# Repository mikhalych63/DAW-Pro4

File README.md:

This is a project of car audio processor and 8ch amplifier wich use of CamillaDSP project: https://github.com/HEnquist/camilladsp

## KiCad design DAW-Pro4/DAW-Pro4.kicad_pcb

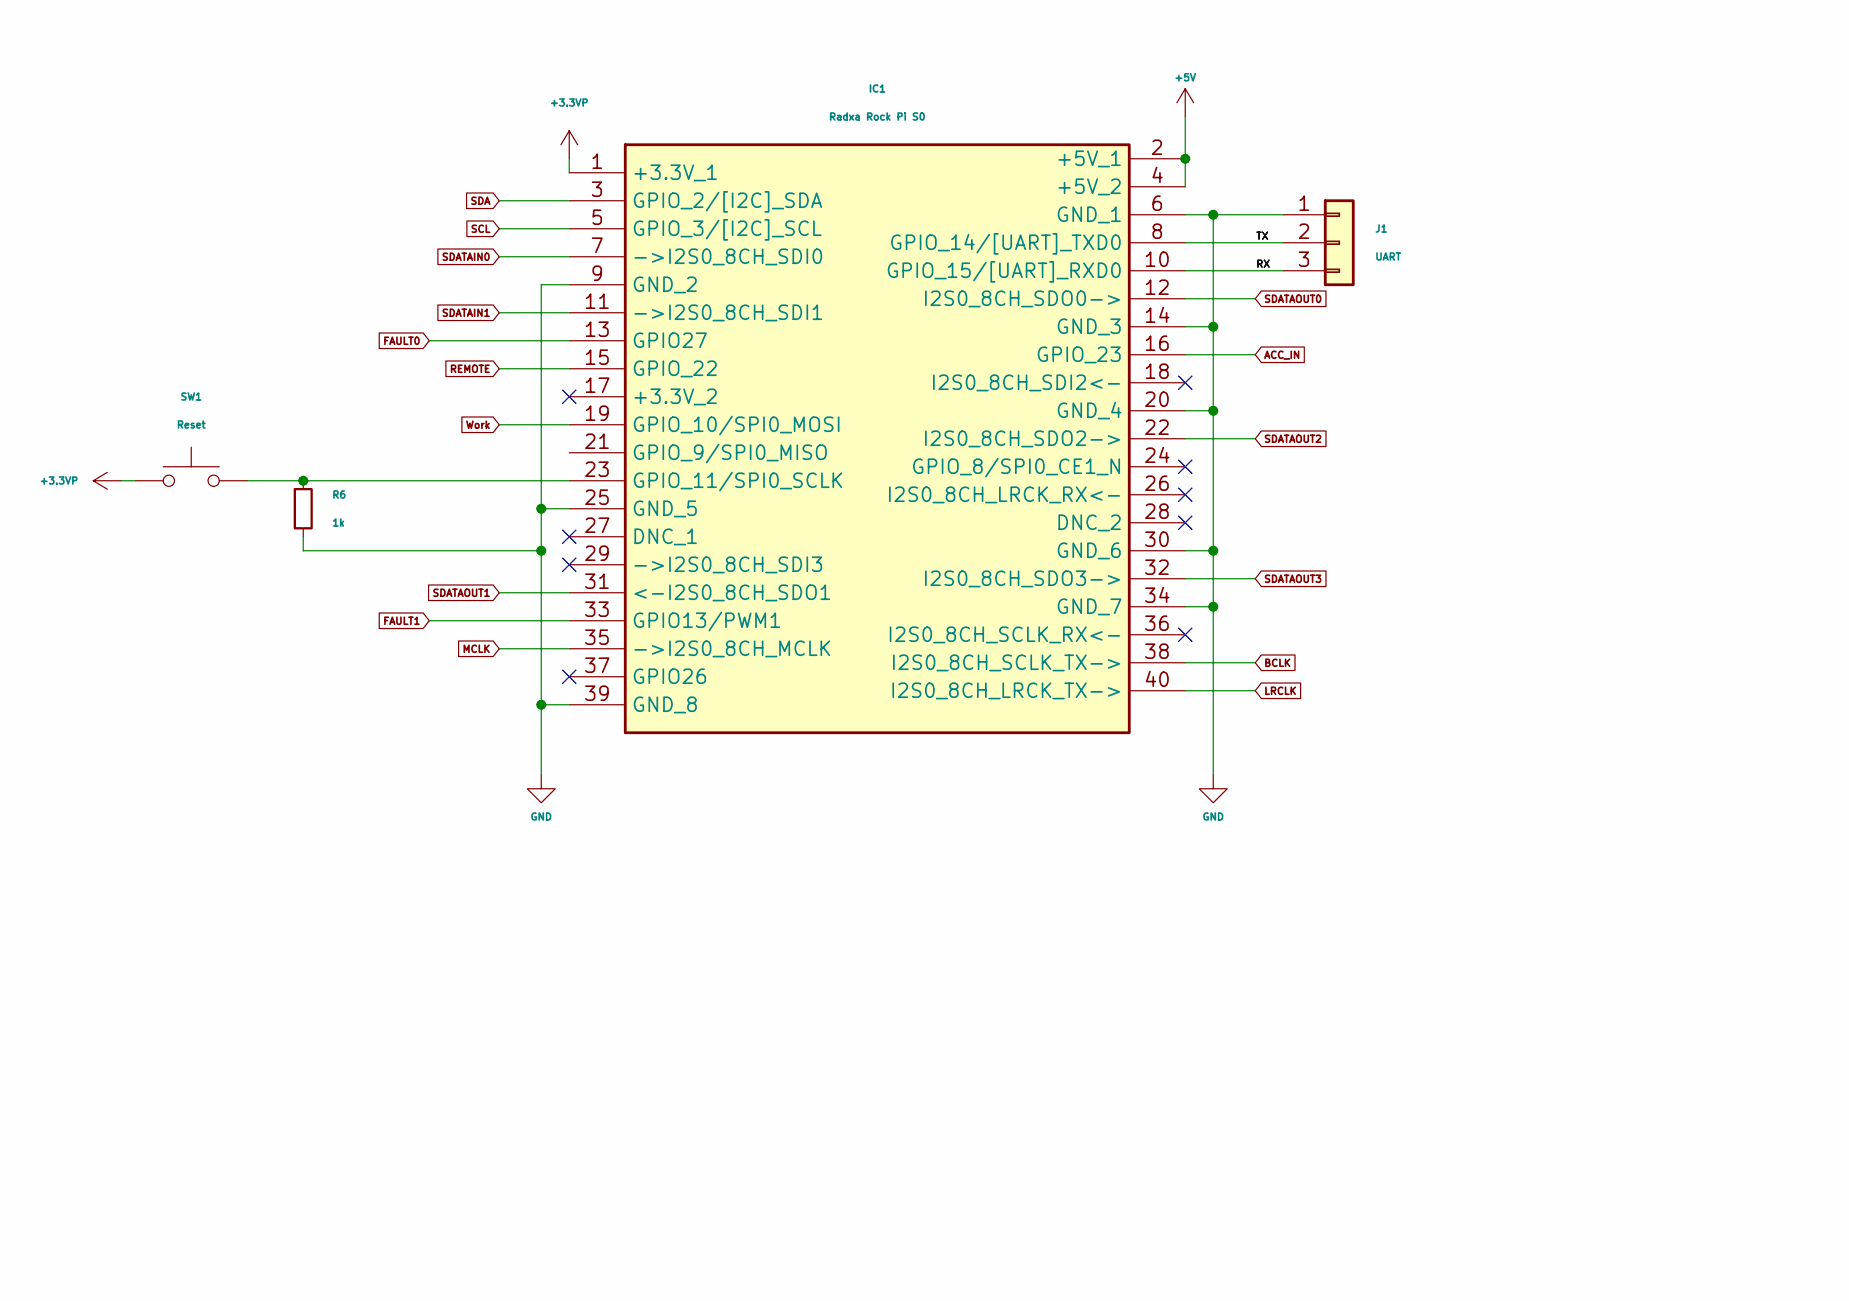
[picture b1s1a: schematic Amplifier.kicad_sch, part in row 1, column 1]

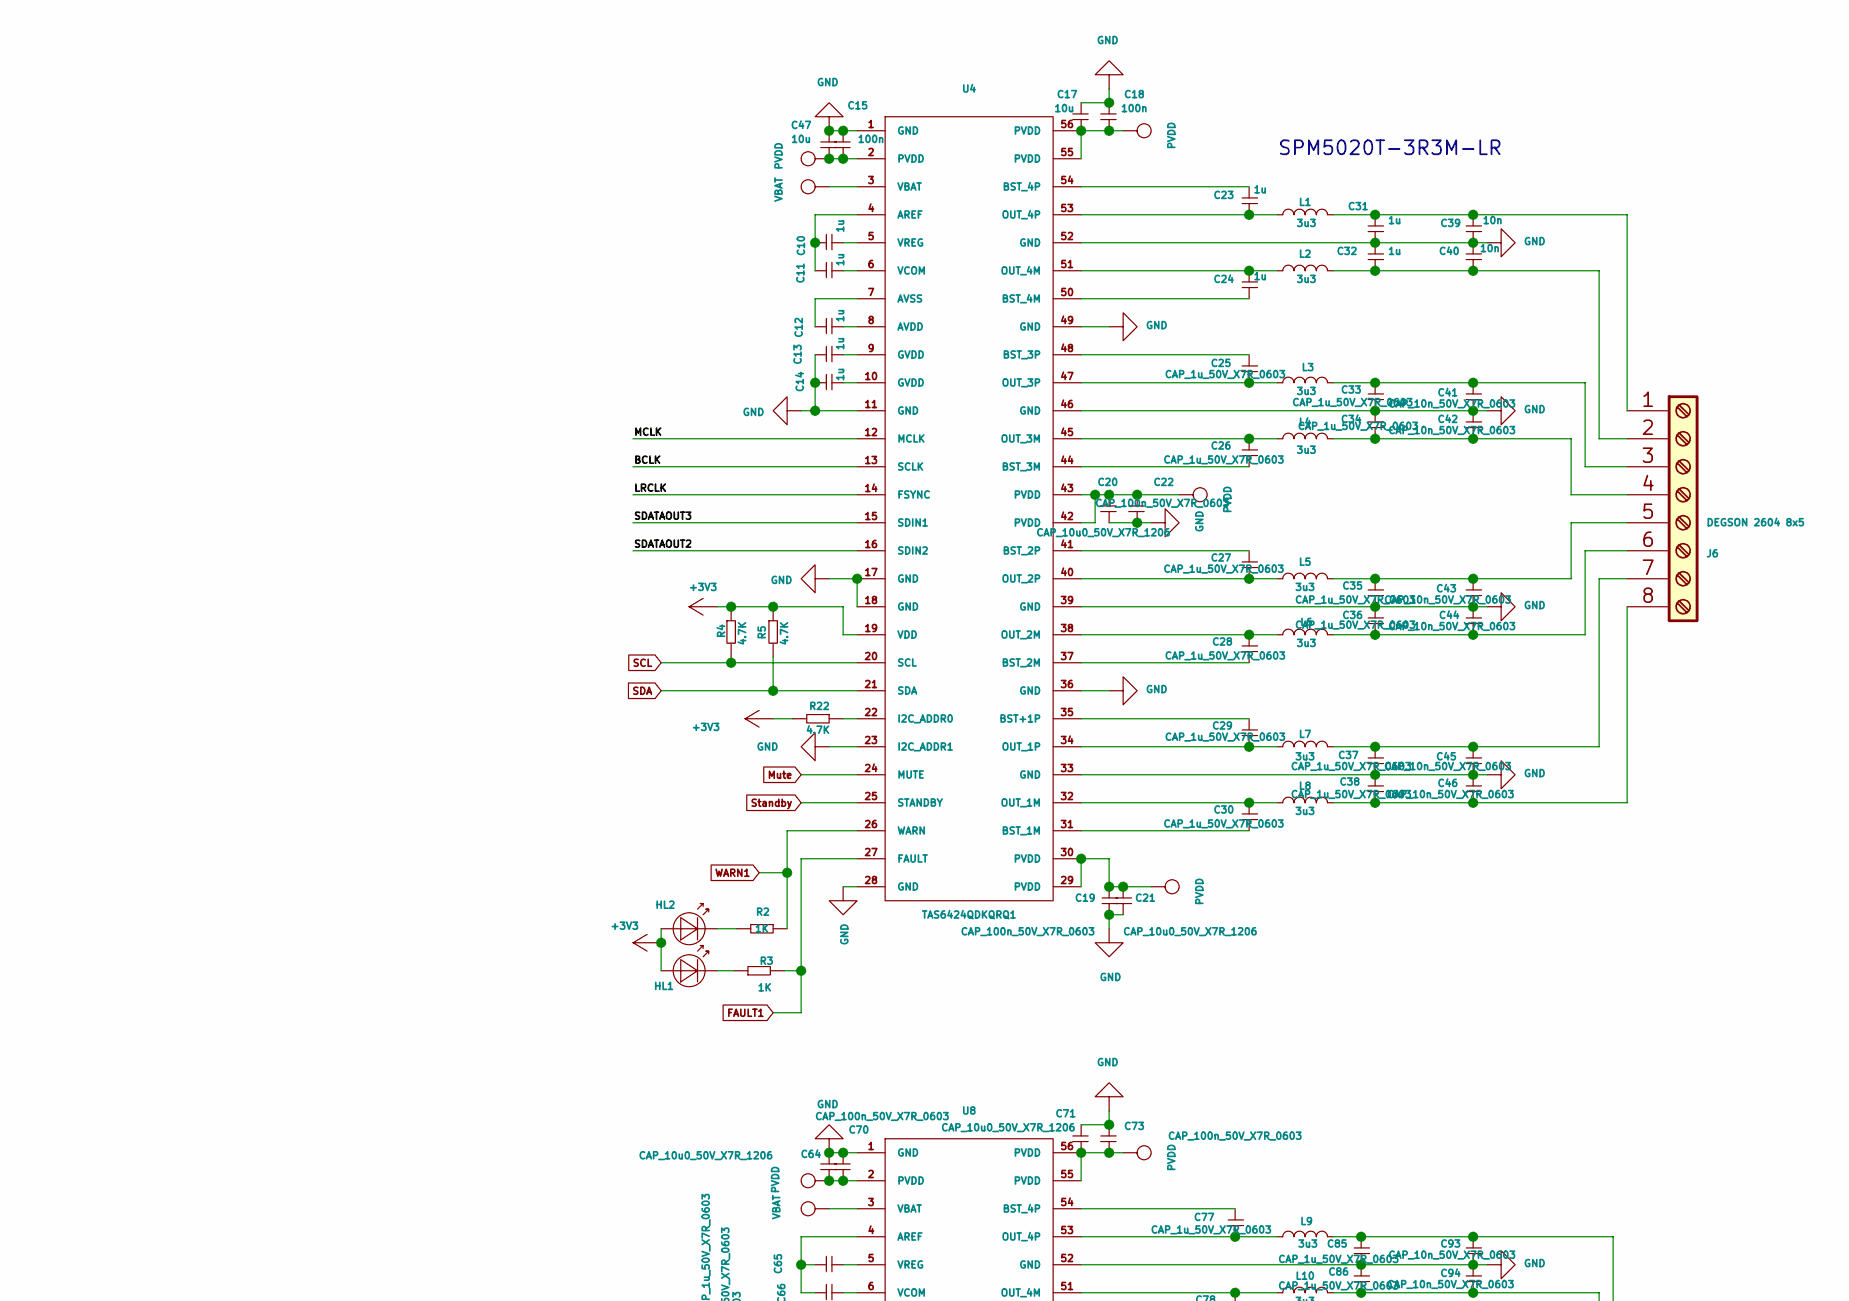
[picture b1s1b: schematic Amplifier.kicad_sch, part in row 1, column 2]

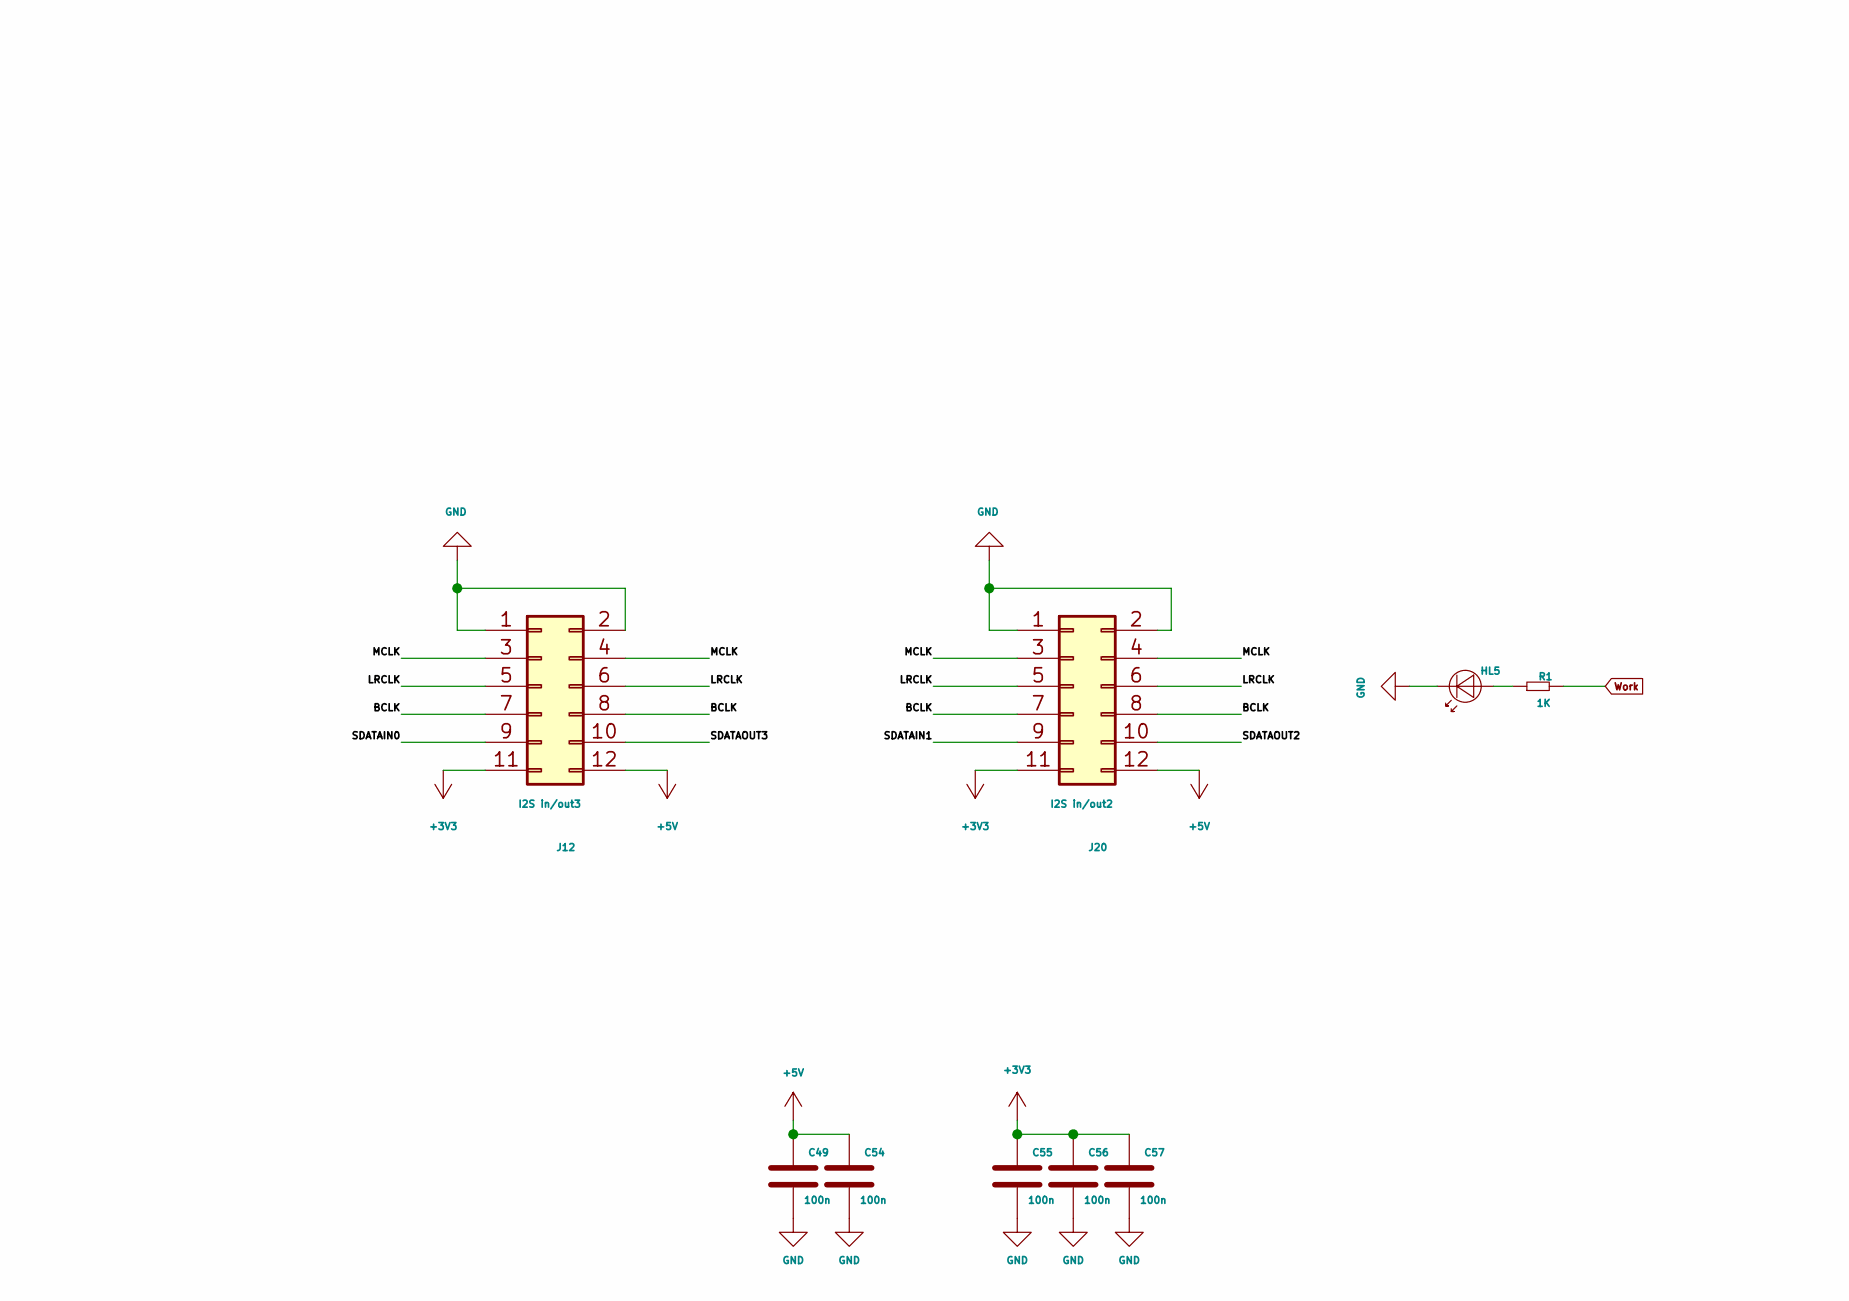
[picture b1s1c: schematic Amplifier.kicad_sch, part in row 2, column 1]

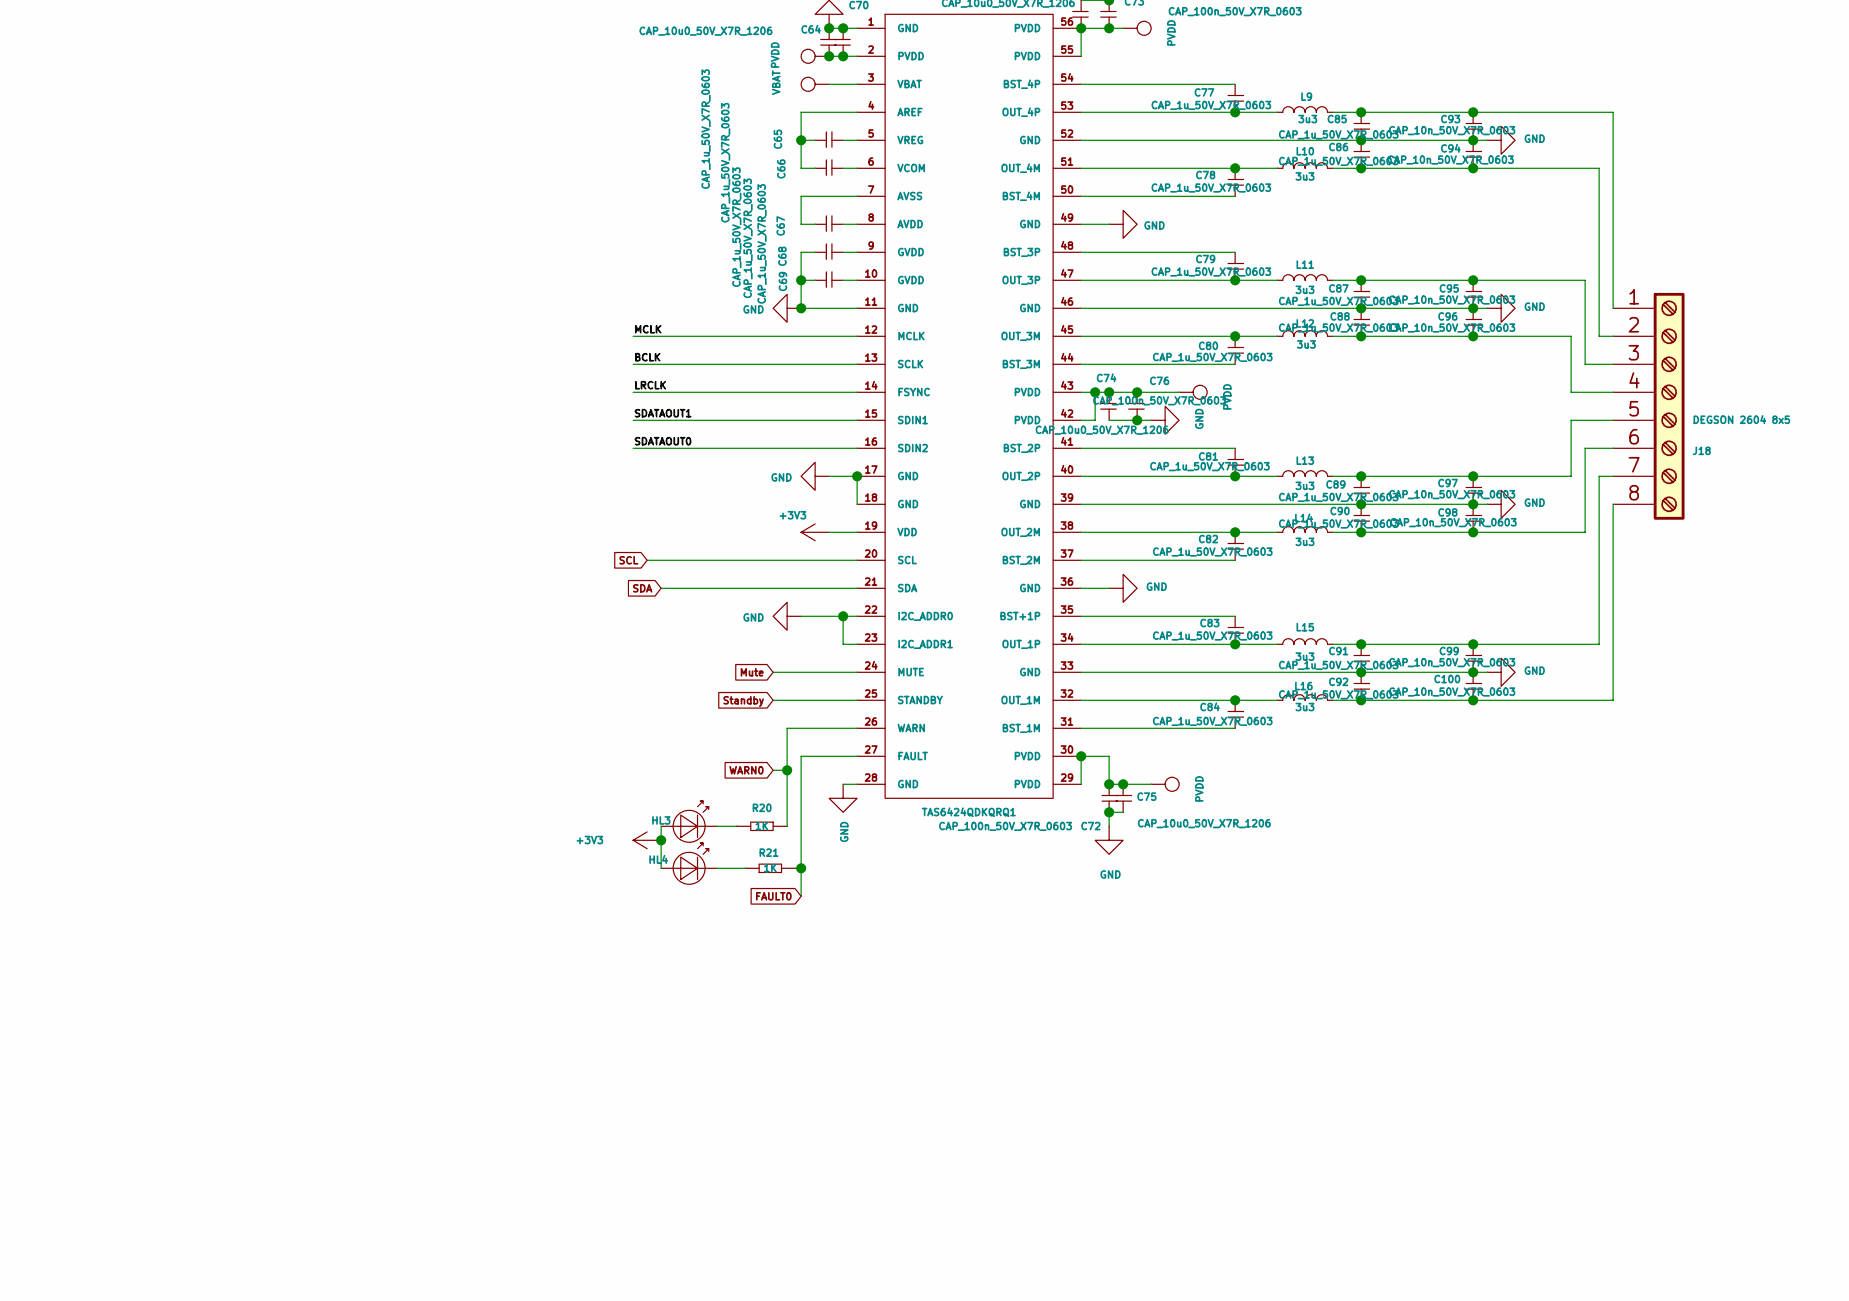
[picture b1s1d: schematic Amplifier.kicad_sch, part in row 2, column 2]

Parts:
C10, C11, C12, C13, C14, C23, C24, C25, C26, C27, C28, C29, C30, C31, C32, C33, C34, C35, C36, C37, C38, C65, C66, C67, C68, C69, C77, C78, C79, C80, C81, C82, C83, C84, C85, C86, C87, C88, C89, C90, C91, C92: CAP_1u_50V_X7R_0603; C_0603_1608Metric
C15, C18, C19, C22, C70, C72, C73, C76: CAP_100n_50V_X7R_0603; C_0603_1608Metric
C17, C20, C21, C47, C64, C71, C74, C75: CAP_10u0_50V_X7R_1206; C_1206_3216Metric
C39, C40, C41, C42, C43, C44, C45, C46, C93, C94, C95, C96, C97, C98, C99, C100: CAP_10n_50V_X7R_0603; C_0603_1608Metric
C49: CAP_10n_50V_X7R_0603; C_0603_1608Metric; digikey 399-1170-1-ND
C54, C55, C56, C57: CAP_100n_50V_X7R_0603; C_0603_1608Metric; digikey 399-1170-1-ND
HL1, HL4: LED_SMD_0603_YELLOW; LED_0603_1608Metric
HL2, HL3: LED_SMD_0603_RED; LED_0603_1608Metric
HL5: LED_SMD_0603_YELLOW; LED_D3.0mm_Horizontal_O6.35mm_Z10.0mm
IC1: Radxa Rock Pi S0; RockPiS0; Manufacturer_Part_Number Raspberry Pi Zero W (v1.3)
J1: UART; PinHeader_1x03_P2.54mm_Vertical
J6, J18: DEGSON 2604 8x5; DG271R-5.0-08P
J12, J20: Conn_edge_2x6_2.54_Male; 2x6
L1, L2, L3, L4, L5, L6, L7, L8, L9, L10, L11, L12, L13, L14, L15, L16: 3u3; SPM5010-5020
R1, R2, R3, R20, R21: 1K; R_0603_1608Metric
R4, R5, R22: 4.7K; R_0603_1608Metric
R6: 1k; R_0603_1608Metric
SW1: Reset; SW_Tactile_SPST_Angled_PTS645Vx58-2LFS
U4, U8: TAS6424QDKQRQ1; SSOP-56_7.5x18.5mm_P0.635mm

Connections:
+3.3VP: IC1.1 (+3.3V_1), SW1.1; also elsewhere on the board
+3V3: C55.1, C56.1, C57.1, HL1.2 (A), HL2.2 (A), HL3.2 (A), HL4.2 (A), J12.11, J20.11, R4.1, R5.1, R22.2, U4.19 (VDD), U8.19 (VDD); also elsewhere on the board
+5V: C49.1, C54.1, IC1.2 (+5V_1), IC1.4 (+5V_2), J12.12, J20.12; also elsewhere on the board
/Amplifier/RX: IC1.10 (GPIO_15/[UART]_RXD0), J1.3
/Amplifier/TX: IC1.8 (GPIO_14/[UART]_TXD0), J1.2
ACC_IN: IC1.16 (GPIO_23); also elsewhere on the board
BCLK: IC1.38 (I2S0_8CH_SCLK_TX->), J12.7, J12.8, J20.7, J20.8, U4.13 (SCLK), U8.13 (SCLK)
FAULT0: IC1.13 (GPIO27), R21.2, U8.27 (FAULT)
FAULT1: IC1.33 (GPIO13/PWM1), R3.2, U4.27 (FAULT)
GND: C13.2, C14.2, C15.1, C17.1, C18.1, C19.1, C20.2, C21.1, C22.2, C31.1, C32.2, C33.1, C34.2, C35.1, C36.2, C37.1, C38.2, C39.1, C40.2, C41.1, C42.2, C43.1, C44.2, C45.1, C46.2, C47.1, C49.2, C54.2, C55.2, C56.2, C57.2, C64.1, C68.2, C69.2, C70.1, C71.1, C72.1, C73.1, C74.2, C75.1, C76.2, C85.1, C86.2, C87.1, C88.2, C89.1, C90.2, C91.1, C92.2, C93.1, C94.2, C95.1, C96.2, C97.1, C98.2, C99.1, C100.2, HL5.1 (K), IC1.6 (GND_1), IC1.9 (GND_2), IC1.14 (GND_3), IC1.20 (GND_4), IC1.25 (GND_5), IC1.30 (GND_6), IC1.34 (GND_7), IC1.39 (GND_8), J1.1, J12.1, J12.2, J20.1, J20.2, R6.2, U4.1 (GND), U4.11 (GND), U4.17 (GND), U4.18 (GND), U4.23 (I2C_ADDR1), U4.28 (GND), U4.33 (GND), U4.36 (GND), U4.39 (GND), U4.46 (GND), U4.49 (GND), U4.52 (GND), U8.1 (GND), U8.11 (GND), U8.17 (GND), U8.18 (GND), U8.22 (I2C_ADDR0), U8.23 (I2C_ADDR1), U8.28 (GND), U8.33 (GND), U8.36 (GND), U8.39 (GND), U8.46 (GND), U8.49 (GND), U8.52 (GND); also elsewhere on the board
LRCLK: IC1.40 (I2S0_8CH_LRCK_TX->), J12.5, J12.6, J20.5, J20.6, U4.14 (FSYNC), U8.14 (FSYNC)
MCLK: IC1.35 (->I2S0_8CH_MCLK), J12.3, J12.4, J20.3, J20.4, U4.12 (MCLK), U8.12 (MCLK)
Mute: U4.24 (MUTE), U8.24 (MUTE)
unnamed: C13.1, U4.9 (GVDD)
unnamed: C14.1, U4.10 (GVDD)
unnamed: C68.1, U8.9 (GVDD)
unnamed: C69.1, U8.10 (GVDD)
unnamed: HL1.1 (K), R3.1
unnamed: HL2.1 (K), R2.2
unnamed: HL3.1 (K), R20.2
unnamed: HL4.1 (K), R21.1
unnamed: HL5.2 (A), R1.1
unnamed: IC1.23 (GPIO_11/SPI0_SCLK), R6.1, SW1.2
unnamed: C31.2, C39.2, J6.1, L1.2
unnamed: C32.1, C40.1, J6.2, L2.2
unnamed: C33.2, C41.2, J6.3, L3.2
unnamed: C34.1, C42.1, J6.4, L4.2
unnamed: C35.2, C43.2, J6.5, L5.2
unnamed: C36.1, C44.1, J6.6, L6.2
unnamed: C37.2, C45.2, J6.7, L7.2
unnamed: C38.1, C46.1, J6.8, L8.2
unnamed: C85.2, C93.2, J18.1, L9.2
unnamed: C86.1, C94.1, J18.2, L10.2
unnamed: C87.2, C95.2, J18.3, L11.2
unnamed: C88.1, C96.1, J18.4, L12.2
unnamed: C89.2, C97.2, J18.5, L13.2
unnamed: C90.1, C98.1, J18.6, L14.2
unnamed: C91.2, C99.2, J18.7, L15.2
unnamed: C92.1, C100.1, J18.8, L16.2
unnamed: C10.2, C11.2, U4.4 (AREF)
unnamed: C12.1, U4.8 (AVDD)
unnamed: C12.2, U4.7 (AVSS)
unnamed: C29.2, U4.35 (BST+1P)
unnamed: C30.1, U4.31 (BST_1M)
unnamed: C28.1, U4.37 (BST_2M)
unnamed: C27.2, U4.41 (BST_2P)
unnamed: C26.1, U4.44 (BST_3M)
unnamed: C25.2, U4.48 (BST_3P)
unnamed: C24.1, U4.50 (BST_4M)
unnamed: C23.2, U4.54 (BST_4P)
unnamed: R22.1, U4.22 (I2C_ADDR0)
unnamed: C30.2, L8.1, U4.32 (OUT_1M)
unnamed: C29.1, L7.1, U4.34 (OUT_1P)
unnamed: C28.2, L6.1, U4.38 (OUT_2M)
unnamed: C27.1, L5.1, U4.40 (OUT_2P)
unnamed: C26.2, L4.1, U4.45 (OUT_3M)
unnamed: C25.1, L3.1, U4.47 (OUT_3P)
unnamed: C24.2, L2.1, U4.51 (OUT_4M)
unnamed: C23.1, L1.1, U4.53 (OUT_4P)
unnamed: C11.1, U4.6 (VCOM)
unnamed: C10.1, U4.5 (VREG)
unnamed: C65.2, C66.2, U8.4 (AREF)
unnamed: C67.1, U8.8 (AVDD)
unnamed: C67.2, U8.7 (AVSS)
unnamed: C83.2, U8.35 (BST+1P)
unnamed: C84.1, U8.31 (BST_1M)
unnamed: C82.1, U8.37 (BST_2M)
unnamed: C81.2, U8.41 (BST_2P)
unnamed: C80.1, U8.44 (BST_3M)
unnamed: C79.2, U8.48 (BST_3P)
unnamed: C78.1, U8.50 (BST_4M)
unnamed: C77.2, U8.54 (BST_4P)
unnamed: C84.2, L16.1, U8.32 (OUT_1M)
unnamed: C83.1, L15.1, U8.34 (OUT_1P)
unnamed: C82.2, L14.1, U8.38 (OUT_2M)
unnamed: C81.1, L13.1, U8.40 (OUT_2P)
unnamed: C80.2, L12.1, U8.45 (OUT_3M)
unnamed: C79.1, L11.1, U8.47 (OUT_3P)
unnamed: C78.2, L10.1, U8.51 (OUT_4M)
unnamed: C77.1, L9.1, U8.53 (OUT_4P)
unnamed: C66.1, U8.6 (VCOM)
unnamed: C65.1, U8.5 (VREG)
PVDD: C15.2, C17.2, C18.2, C19.2, C20.1, C21.2, C22.1, C47.2, C64.2, C70.2, C71.2, C72.2, C73.2, C74.1, C75.2, C76.1, U4.2 (PVDD), U4.29 (PVDD), U4.30 (PVDD), U4.42 (PVDD), U4.43 (PVDD), U4.55 (PVDD), U4.56 (PVDD), U8.2 (PVDD), U8.29 (PVDD), U8.30 (PVDD), U8.42 (PVDD), U8.43 (PVDD), U8.55 (PVDD), U8.56 (PVDD); also elsewhere on the board
REMOTE: IC1.15 (GPIO_22); also elsewhere on the board
SCL: IC1.5 (GPIO_3/[I2C]_SCL), R4.2, U4.20 (SCL), U8.20 (SCL)
SDA: IC1.3 (GPIO_2/[I2C]_SDA), R5.2, U4.21 (SDA), U8.21 (SDA)
SDATAIN0: IC1.7 (->I2S0_8CH_SDI0), J12.9
SDATAIN1: IC1.11 (->I2S0_8CH_SDI1), J20.9
SDATAOUT0: IC1.12 (I2S0_8CH_SDO0->), U8.16 (SDIN2)
SDATAOUT1: IC1.31 (<-I2S0_8CH_SDO1), U8.15 (SDIN1)
SDATAOUT2: IC1.22 (I2S0_8CH_SDO2->), J20.10, U4.16 (SDIN2)
SDATAOUT3: IC1.32 (I2S0_8CH_SDO3->), J12.10, U4.15 (SDIN1)
Standby: U4.25 (STANDBY), U8.25 (STANDBY)
VBAT: U4.3 (VBAT), U8.3 (VBAT); also elsewhere on the board
WARN0: R20.1, U8.26 (WARN)
WARN1: R2.1, U4.26 (WARN)
Work: IC1.19 (GPIO_10/SPI0_MOSI), R1.2

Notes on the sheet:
SPM5020T-3R3M-LR

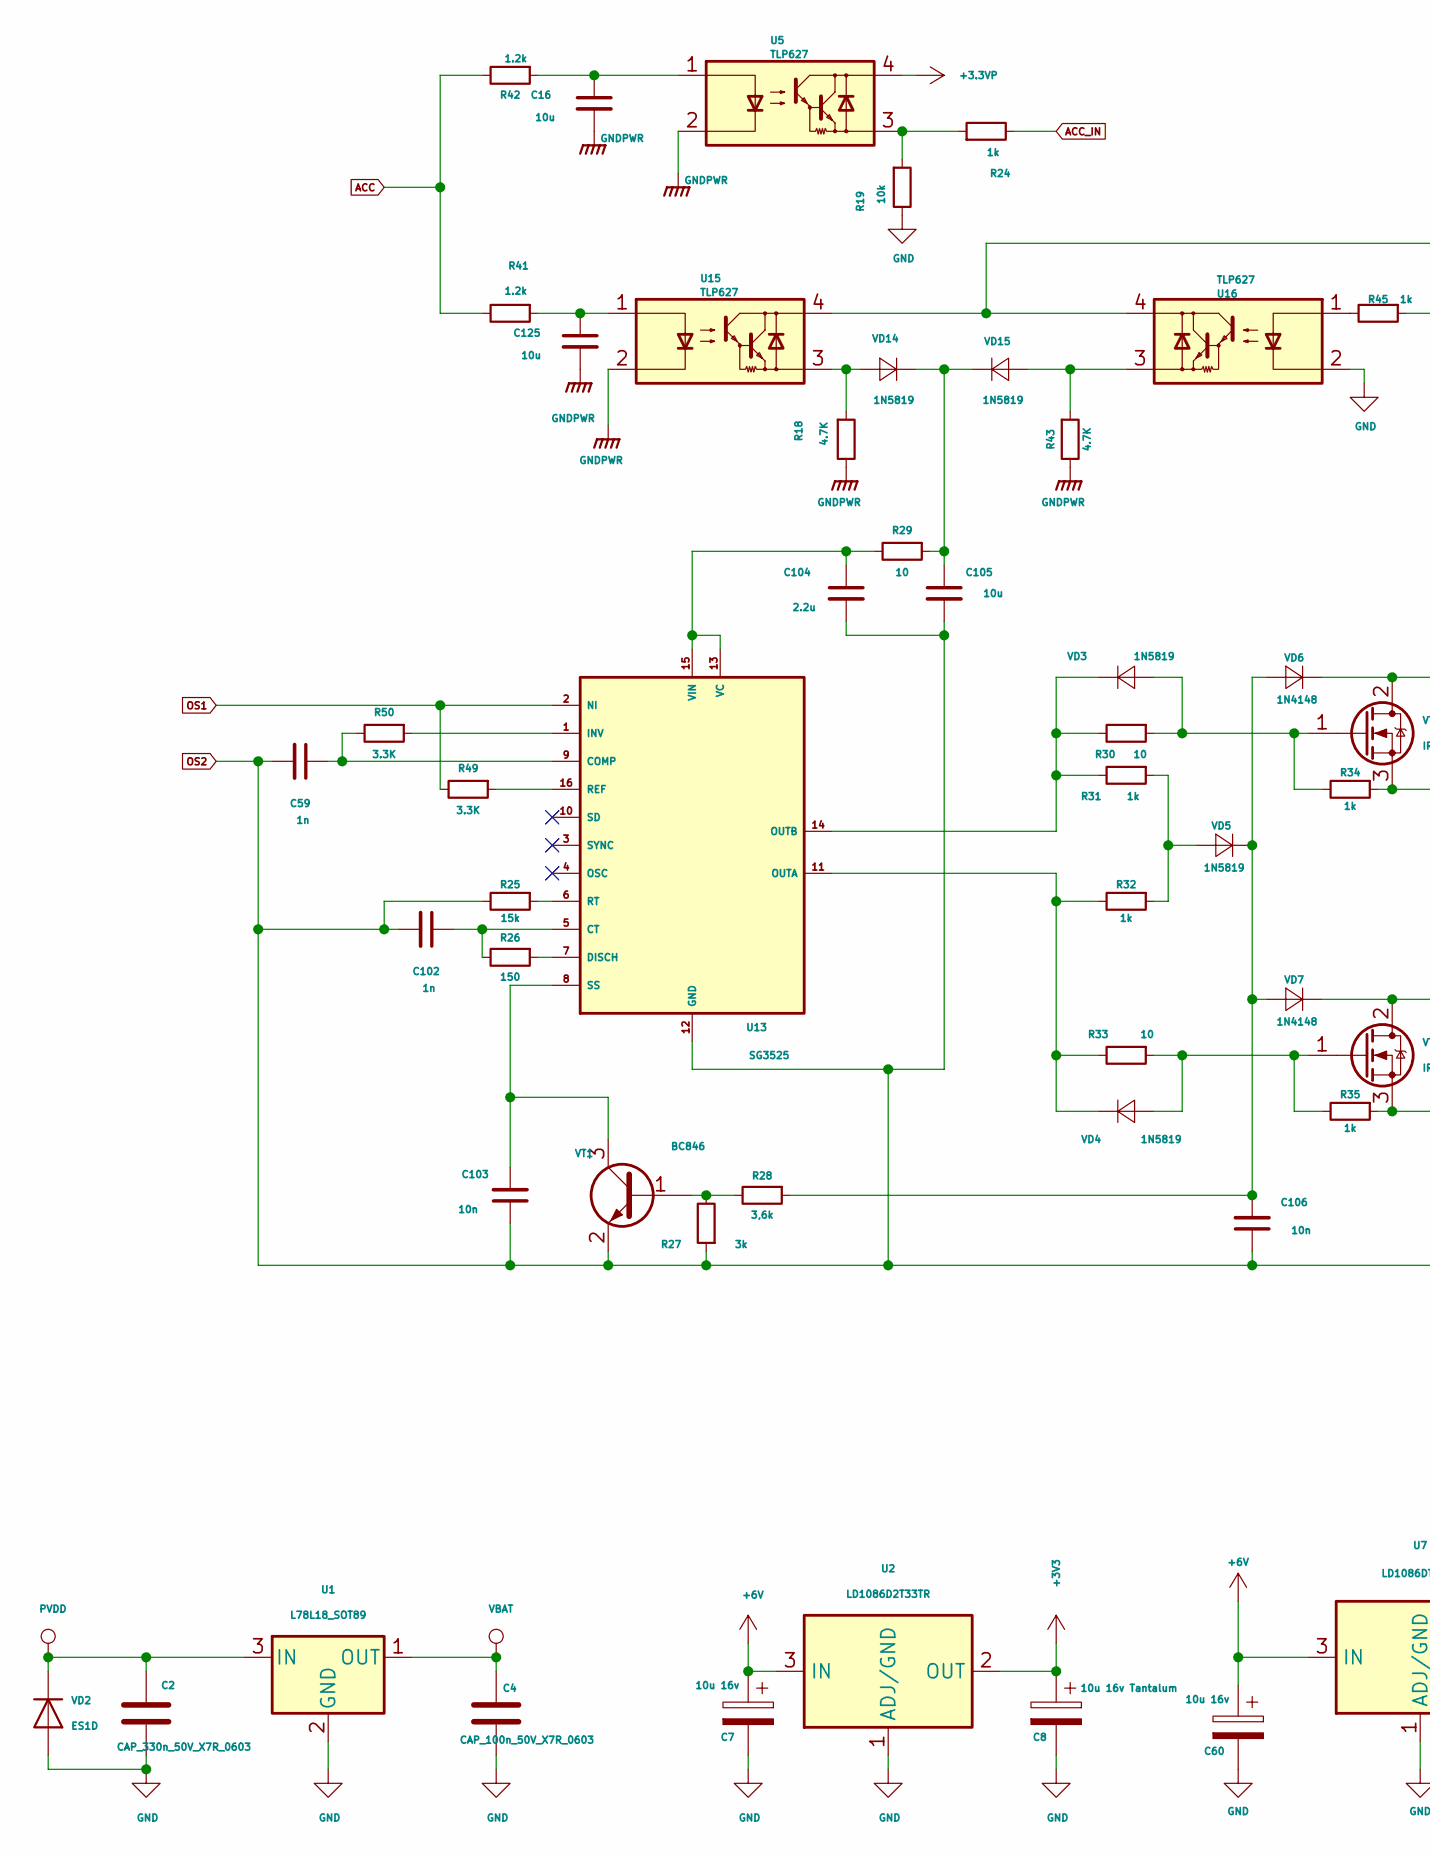
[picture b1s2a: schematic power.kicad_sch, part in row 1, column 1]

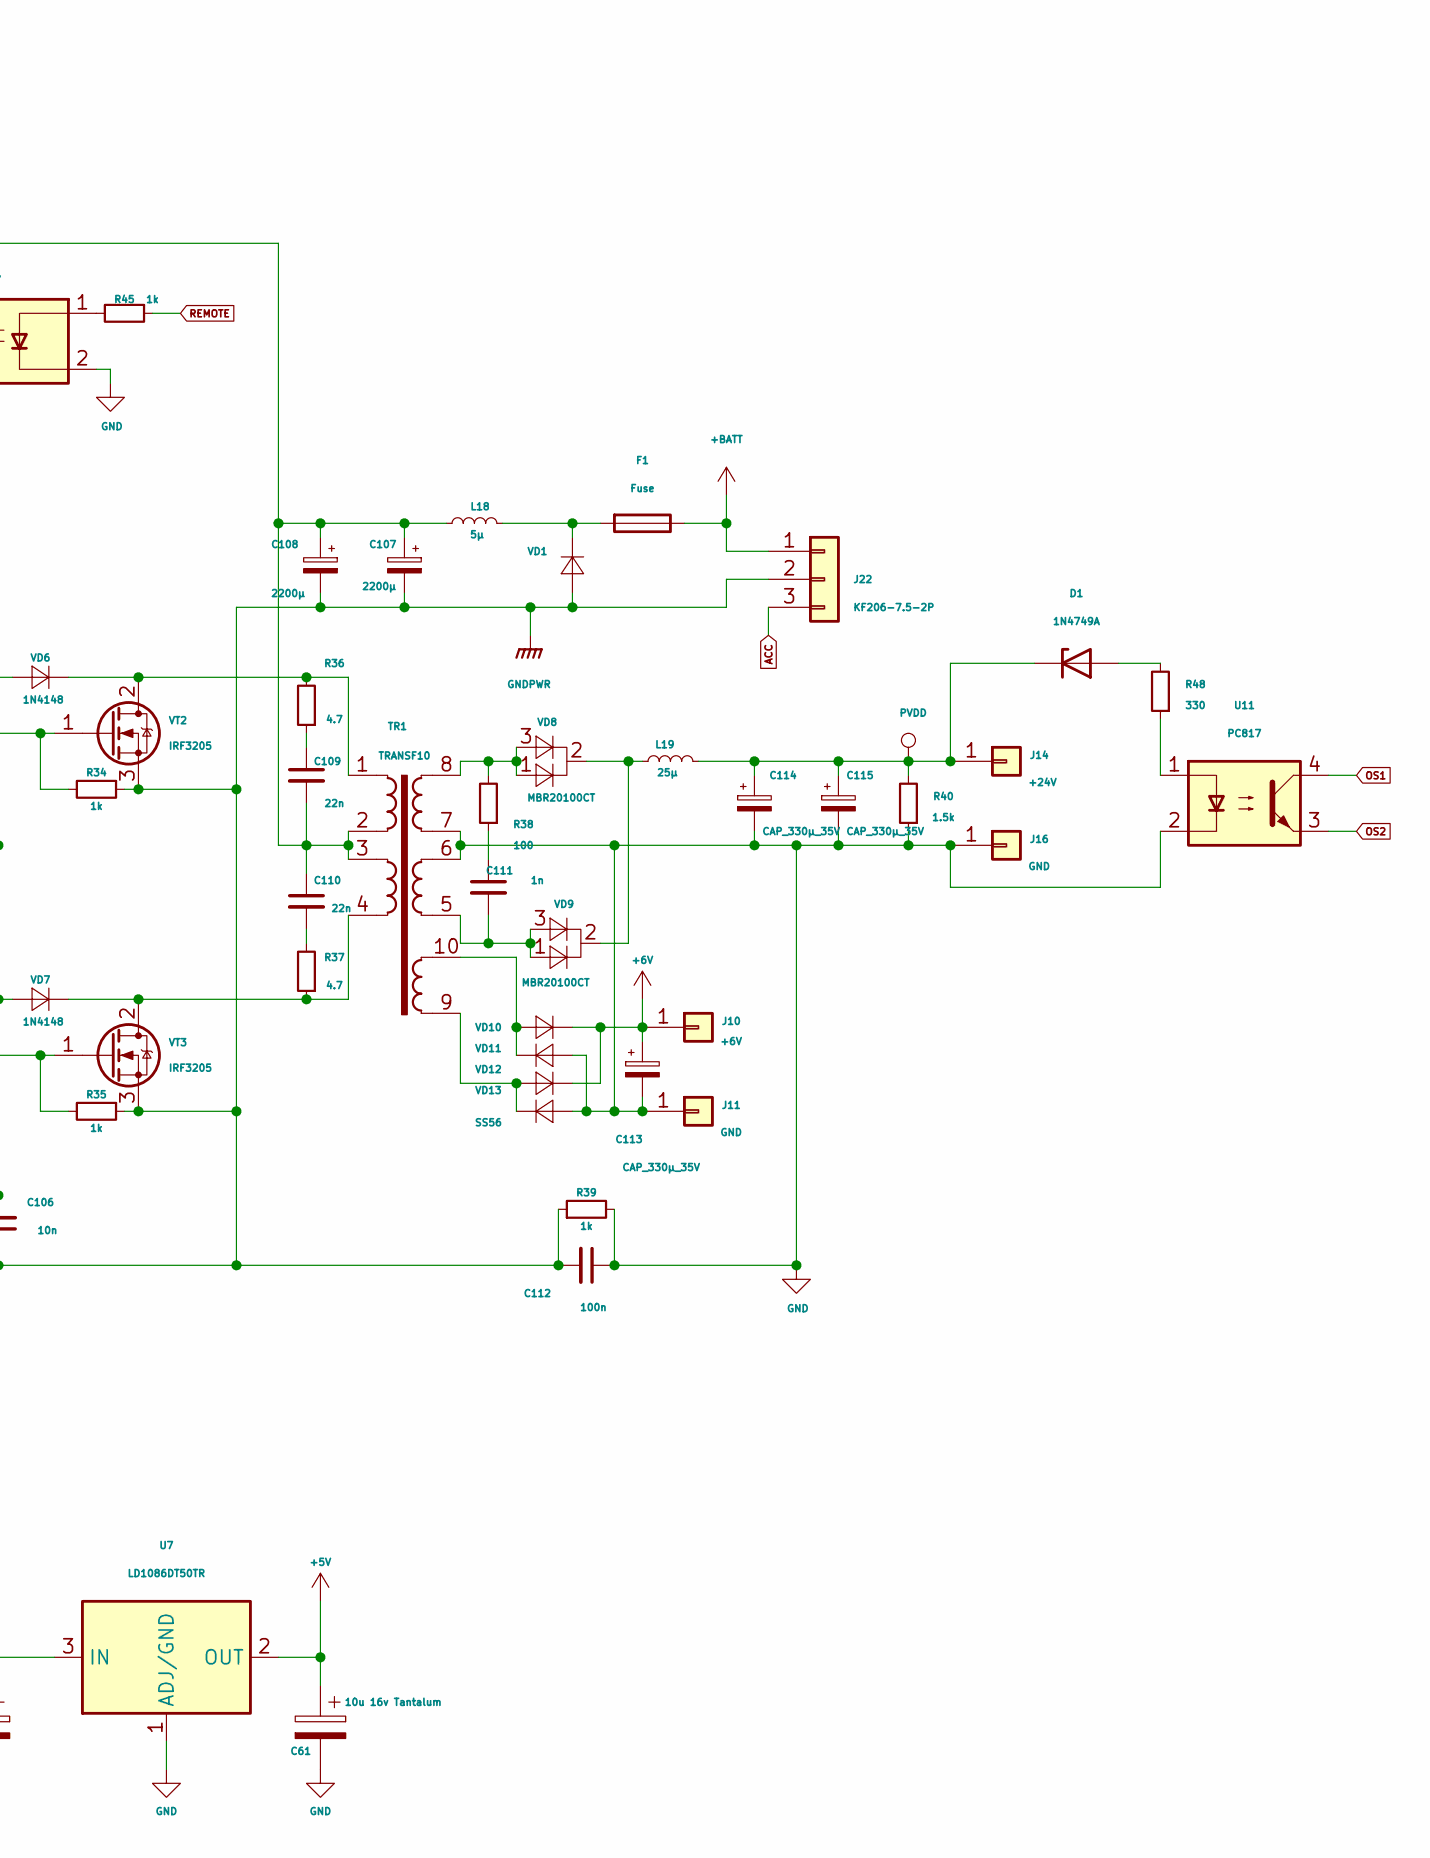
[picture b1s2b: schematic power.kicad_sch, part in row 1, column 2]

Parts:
C2: CAP_330n_50V_X7R_0603; C_0603_1608Metric
C4, C112: CAP_100n_50V_X7R_0603; C_0603_1608Metric
C7, C60: 10u 16v; CP_Elec_8x10
C8, C61: 10u 16v Tantalum; CP_EIA-3216-18_Kemet-A
C16, C105, C125: CAP_10u0_50V_X7R_1206; C_1206_3216Metric
C59, C102, C111: CAP_1n_50V_X7R_0603; C_0603_1608Metric
C103, C106: CAP_10n_50V_X7R_0603; C_0603_1608Metric
C104: CAP_2u2_50V_X7R_1206; C_1206_3216Metric
C107, C108: 2200μ; CP_Radial_D14.0mm_P5.00mm
C109, C110: CAP_22n_50V_X7R_0603; C_0603_1608Metric
C113, C114, C115: CAP_330μ_35V; CP_Radial_D10.0mm_P5.00mm
D1: 1N4749A; D_DO-34_SOD68_P7.62mm_Horizontal
F1: Fuse; Fuse_Blade_vertical
J10: +6V; TestPoint_Pad_1.5x1.5mm
J11, J16: GND; TestPoint_Pad_1.5x1.5mm
J14: +24V; TestPoint_Pad_1.5x1.5mm
J22: KF206-7.5-2P; DG271R-5.0-03P
L18: 5μ; L_Axial_L26.0mm_D9.0mm_P5.08mm_Vertical
L19: 25μ; L_Toroid_Vertical_L33.0mm_W17.8mm_P12.70mm_Pulse_KM-5
R18, R43: 4.7K; R_0603_1608Metric
R19: 10k; R_0603_1608Metric
R24, R31, R32, R34, R35, R39, R45: 1k; R_0603_1608Metric
R25: 15k; R_0603_1608Metric
R26: 150; R_0603_1608Metric
R27: 3k; R_0603_1608Metric
R28: 3,6k; R_0603_1608Metric
R29, R30, R33: 10; R_0603_1608Metric
R36, R37: 4.7; R_Axial_DIN0204_L3.6mm_D1.6mm_P5.08mm_Vertical
R38: 100; R_Axial_DIN0204_L3.6mm_D1.6mm_P5.08mm_Vertical
R40: 1.5k; R_Axial_DIN0204_L3.6mm_D1.6mm_P5.08mm_Vertical
R41, R42: 1.2k; R_1206_3216Metric
R48: 330; R_0603_1608Metric
R49, R50: 3.3K; R_0603_1608Metric
TR1: TRANSF10; Transformer_ETD44_Horizontal
U1: L78L18_SOT89; SOT-89-3
U2: LD1086D2T33TR; TO-263-2
U5, U15, U16: TLP627; DIP-4_W7.62mm
U7: LD1086DT50TR; TO-263-2
U11: PC817; DIP-4_W7.62mm
U13: SG3525; SOIC-16_3.9x9.9mm_P1.27mm
VD1, VD10, VD11, VD12, VD13: SS56; D_SMC
VD2: ES1D; D_SMA
VD3, VD4, VD5, VD14, VD15: 1N5819; D_SMA
VD6, VD7: 1N4148; D_SMA
VD8, VD9: MBR20100CT; TO-220-3_Horizontal_TabUp
VT1: BC846; SOT-23
VT2, VT3: IRF3205; TO-220-3_Horizontal_TabUp

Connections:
+3.3VP: U5.4; also elsewhere on the board
+3V3: C8.1, U2.2 (OUT); also elsewhere on the board
+5V: C61.1, U7.2 (OUT); also elsewhere on the board
+6V: C7.1, C60.1, C113.1, J10.1, U2.3 (IN), U7.3 (IN), VD10.1 (K), VD12.1 (K)
+BATT: F1.1, J22.1
ACC: J22.3, R41.2, R42.2
ACC_IN: R24.2; also elsewhere on the board
GND: C2.2, C4.2, C7.2, C8.2, C60.2, C61.2, C112.1, C113.2, C114.2, C115.2, J11.1, J16.1, R19.2, R39.2, R40.1, TR1.6, TR1.7, U1.2 (GND), U2.1 (ADJ/GND), U7.1 (ADJ/GND), U11.2, U16.2, VD2.2 (A), VD11.2 (A), VD13.2 (A); also elsewhere on the board
unnamed: C16.1, R42.1, U5.1
unnamed: C107.1, C108.1, C109.2, C110.1, L18.2, TR1.2, TR1.3, U15.4, U16.4
unnamed: C109.1, R36.1
unnamed: C110.2, R37.2
unnamed: C111.1, R38.1
unnamed: C125.1, R41.1, U15.1
unnamed: D1.2 (A), R48.2
unnamed: R19.1, R24.1, U5.3
unnamed: R45.2, U16.1
unnamed: R48.1, U11.1
unnamed: C59.1, R50.2, U13.9 (COMP)
unnamed: C102.1, R26.2, U13.5 (CT)
unnamed: R26.1, U13.7 (DISCH)
unnamed: R50.1, U13.1 (INV)
unnamed: R32.2, R33.2, U13.11 (OUTA), VD4.1 (K)
unnamed: R30.2, R31.2, U13.14 (OUTB), VD3.1 (K)
unnamed: R49.1, U13.16 (REF)
unnamed: R25.1, U13.6 (RT)
unnamed: C103.2, U13.8 (SS), VT1.3 (C)
unnamed: C104.1, R29.2, U13.13 (VC), U13.15 (VIN)
unnamed: F1.2, L18.1, VD1.1 (K)
unnamed: R30.1, R34.2, VD3.2 (A), VT2.1 (G)
unnamed: R33.1, R35.2, VD4.2 (A), VT3.1 (G)
unnamed: R31.1, R32.1, VD5.2 (A)
unnamed: C106.2, R28.1, VD5.1 (K), VD6.2 (A), VD7.2 (A)
unnamed: R36.2, TR1.1, VD6.1 (K), VT2.2 (D)
unnamed: R37.1, TR1.4, VD7.1 (K), VT3.2 (D)
unnamed: R38.2, TR1.8, VD8.1 (A1), VD8.3 (A2)
unnamed: L19.1, VD8.2 (A), VD9.2 (A)
unnamed: C111.2, TR1.5, VD9.1 (A1), VD9.3 (A2)
unnamed: TR1.10, VD10.2 (A), VD11.1 (K)
unnamed: TR1.9, VD12.2 (A), VD13.1 (K)
unnamed: R18.1, U15.3, VD14.2 (A)
unnamed: C105.1, R29.1, VD14.1 (K), VD15.1 (K)
unnamed: R43.1, U16.3, VD15.2 (A)
unnamed: R27.2, R28.2, VT1.1 (B)
OS1: R49.2, U11.4, U13.2 (NI)
OS2: C16.2, C59.2, C102.2, C103.1, C104.2, C105.2, C106.1, C107.2, C108.2, C112.2, C125.2, J22.2, R18.2, R25.2, R27.1, R34.1, R35.1, R39.1, R43.2, U5.2, U11.3, U13.12 (GND), U15.2, VD1.2 (A), VT1.2 (E), VT2.3 (S), VT3.3 (S)
PVDD: C2.1, C114.1, C115.1, D1.1 (K), J14.1, L19.2, R40.2, U1.3 (IN), VD2.1 (K); also elsewhere on the board
REMOTE: R45.1; also elsewhere on the board
VBAT: C4.1, U1.1 (OUT); also elsewhere on the board
